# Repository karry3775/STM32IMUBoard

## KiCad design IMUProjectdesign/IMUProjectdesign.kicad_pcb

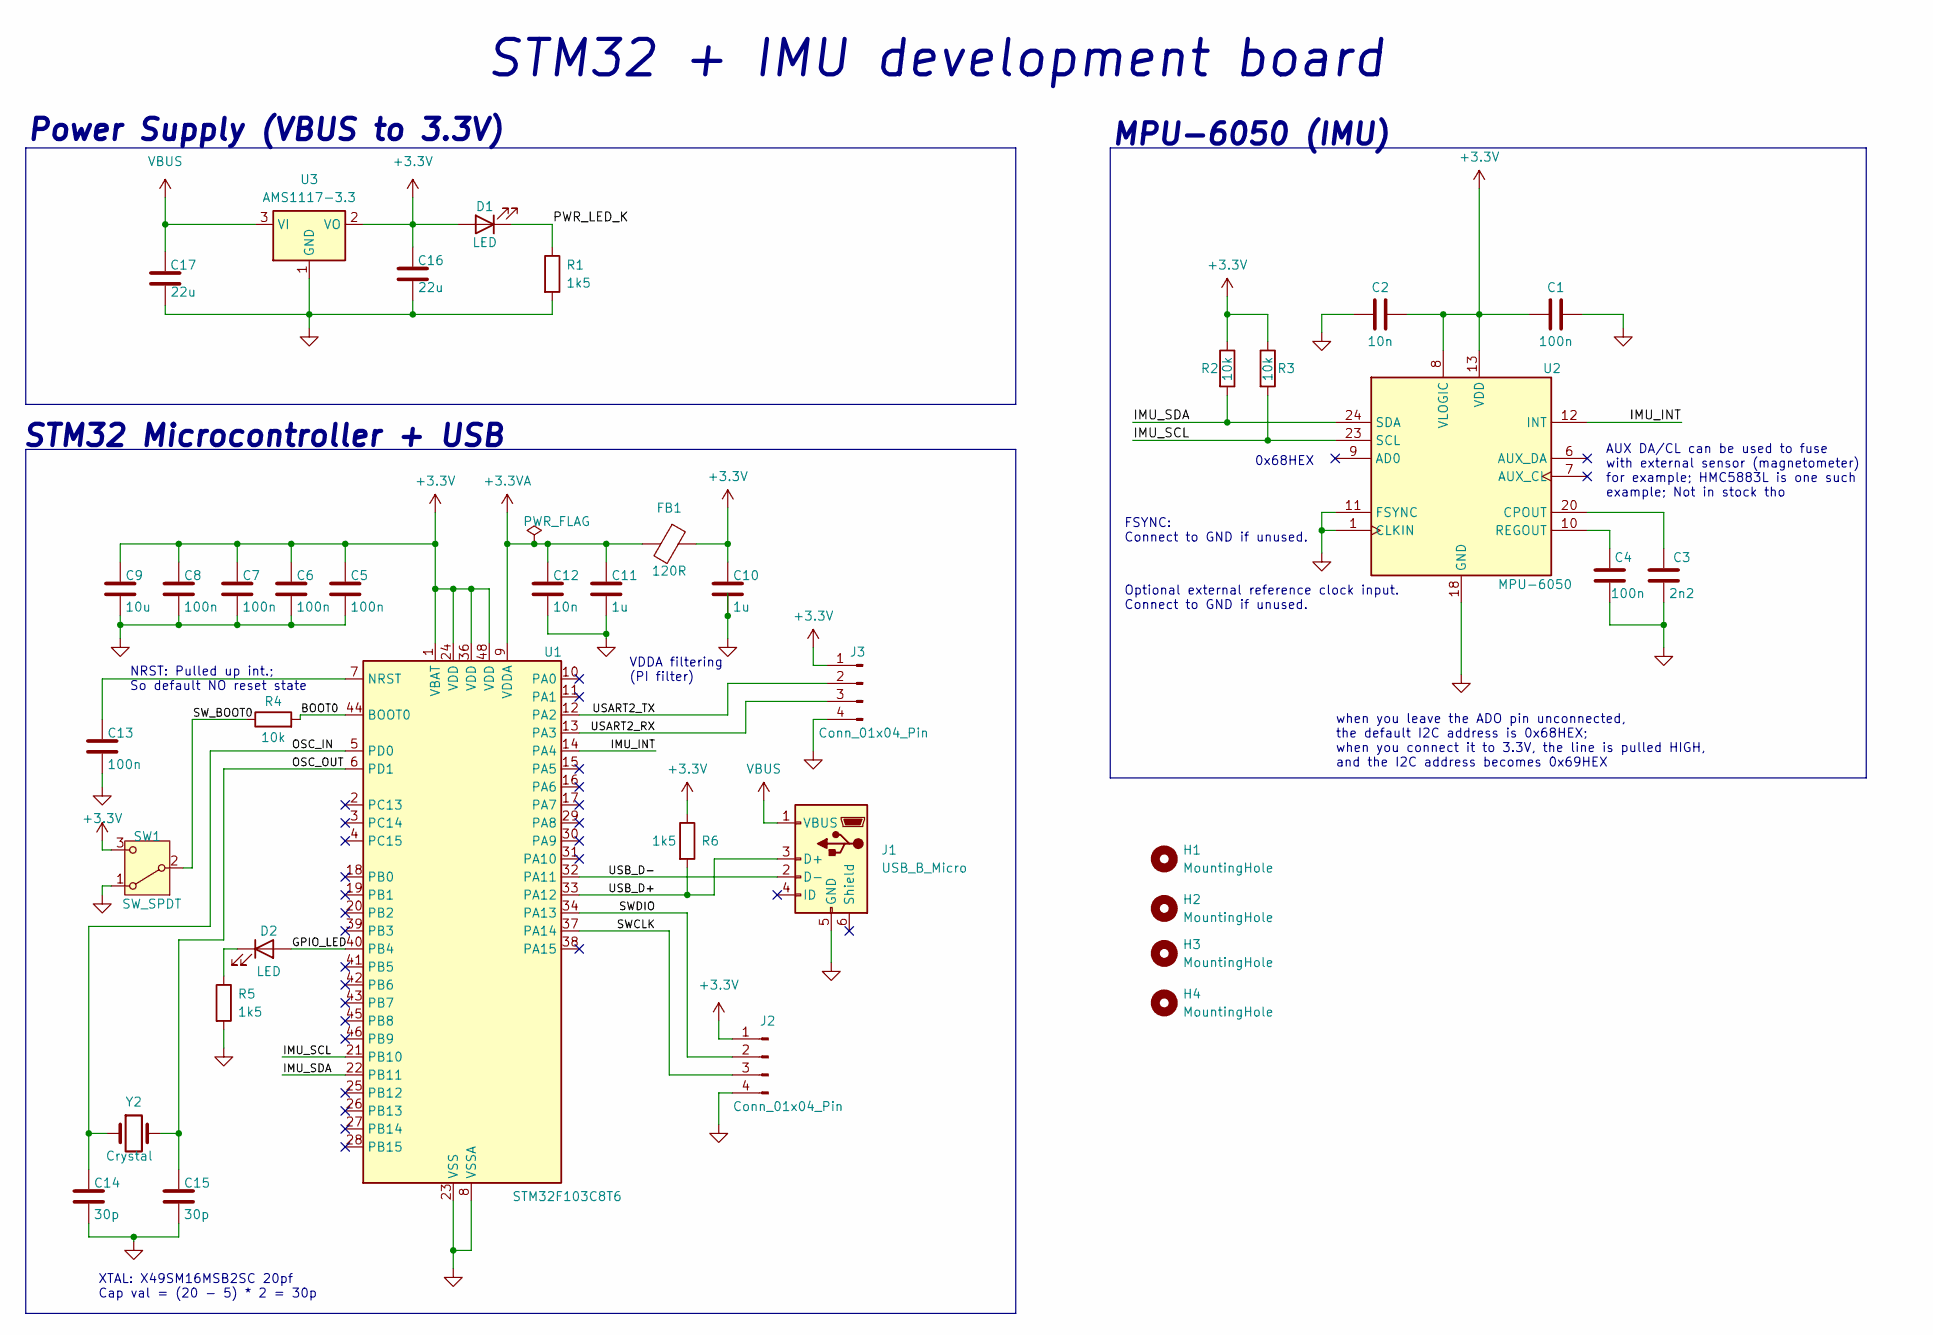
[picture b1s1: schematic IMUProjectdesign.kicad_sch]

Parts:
C1, C4, C5, C6, C7, C8, C13: 100n; C_0402_1005Metric
C2, C12: 10n; C_0402_1005Metric
C3: 2n2; C_0402_1005Metric
C9: 10u; C_0603_1608Metric
C10, C11: 1u; C_0603_1608Metric
C14, C15: 30p; C_0402_1005Metric
C16, C17: 22u; C_0603_1608Metric
D1, D2: LED; LED_0402_1005Metric
FB1: 120R; L_0603_1608Metric
H1, H2, H3, H4: MountingHole; MountingHole_2.2mm_M2_DIN965_Pad_TopBottom
J1: USB_B_Micro; USB_Micro-B_Molex_47346-0001
J2, J3: Conn_01x04_Pin; PinHeader_1x06_P2.54mm_Vertical
R1, R5, R6: 1k5; R_0402_1005Metric
R2, R3, R4: 10k; R_0603_1608Metric
SW1: SW_SPDT; SW_SPDT_PCM12
U1: STM32F103C8T6; LQFP-48_7x7mm_P0.5mm
U2: MPU-6050; InvenSense_QFN-24_4x4mm_P0.5mm
U3: AMS1117-3.3; SOT-223-3_TabPin2
Y2: Crystal; Crystal_SMD_HC49-SD

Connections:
+3.3V: C1.1, C2.2, C5.1, C6.1, C7.1, C8.1, C9.1, C10.1, C16.2, D1.2 (A), FB1.1, J2.1, J3.1, R2.1, R3.1, R6.1, SW1.3 (C), U1.1 (VBAT), U1.24 (VDD), U1.36 (VDD), U1.48 (VDD), U2.8 (VLOGIC), U2.13 (VDD), U3.2 (VO)
+3.3VA: C11.1, C12.1, FB1.2, U1.9 (VDDA)
/BOOT0: R4.2, U1.44 (BOOT0)
/GPIO_LED: D2.2 (A), U1.40 (PB4)
/IMU_INT: U1.14 (PA4), U2.12 (INT)
/IMU_SCL: R3.2, U1.21 (PB10), U2.23 (SCL)
/IMU_SDA: R2.2, U1.22 (PB11), U2.24 (SDA)
/OSC_IN: C14.1, U1.5 (PD0), Y2.1
/OSC_OUT: C15.1, U1.6 (PD1), Y2.2
/PWR_LED_K: D1.1 (K), R1.1
/SWCLK: J2.3, U1.37 (PA14)
/SWDIO: J2.2, U1.34 (PA13)
/SW_BOOT0: R4.1, SW1.2 (B)
/USART2_RX: J3.3, U1.13 (PA3)
/USART2_TX: J3.2, U1.12 (PA2)
/USB_D+: J1.3 (D+), R6.2, U1.33 (PA12)
/USB_D-: J1.2 (D-), U1.32 (PA11)
GND: C1.2, C2.1, C3.1, C4.1, C5.2, C6.2, C7.2, C8.2, C9.2, C10.2, C11.2, C12.2, C13.2, C14.2, C15.2, C16.1, C17.1, J1.5 (GND), J2.4, J3.4, R1.2, R5.2, SW1.1 (A), U1.8 (VSSA), U1.23 (VSS), U1.35 (VSS), U1.47 (VSS), U2.1 (CLKIN), U2.11 (FSYNC), U2.18 (GND), U3.1 (GND)
unnamed: D2.1 (K), R5.1
unnamed: C13.1, U1.7 (NRST)
unnamed: C3.2, U2.20 (CPOUT)
unnamed: C4.2, U2.10 (REGOUT)
VBUS: C17.2, J1.1 (VBUS), U3.3 (VI)

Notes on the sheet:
AUX DA/CL can be used to fuse with external sensor (magnetometer) for example; HMC5883L is one such example; Not in stock tho
XTAL: X49SM16MSB2SC 20pf Cap val = (20 - 5) * 2 = 30p
Power Supply (VBUS to 3.3V)
0x68HEX
STM32 + IMU development board
MPU-6050 (IMU)
Optional external reference clock input. Connect to GND if unused.
when you leave the ADO pin unconnected, the default I2C address is 0x68HEX; when you connect it to 3.3V, the line is pulled HIGH, and the I2C address becomes 0x69HEX
STM32 Microcontroller + USB
VDDA filtering (PI filter)
FSYNC: Connect to GND if unused.
NRST: Pulled up int.; So default NO reset state

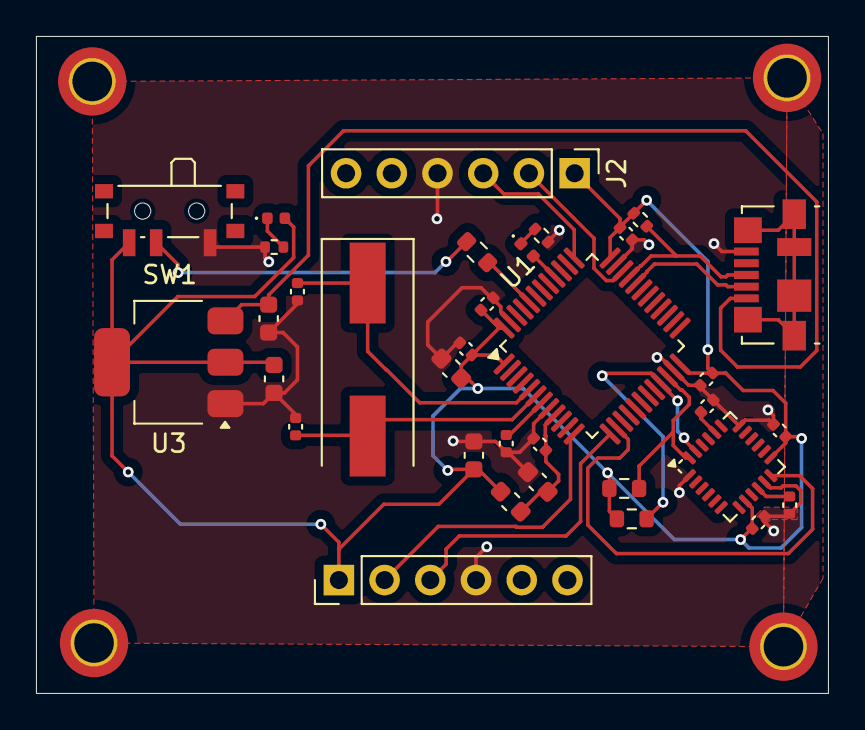
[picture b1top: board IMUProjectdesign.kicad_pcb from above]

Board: 2 copper layers, 44.0 x 36.5 mm, 38 parts (0 on the bottom side), 23 nets.
